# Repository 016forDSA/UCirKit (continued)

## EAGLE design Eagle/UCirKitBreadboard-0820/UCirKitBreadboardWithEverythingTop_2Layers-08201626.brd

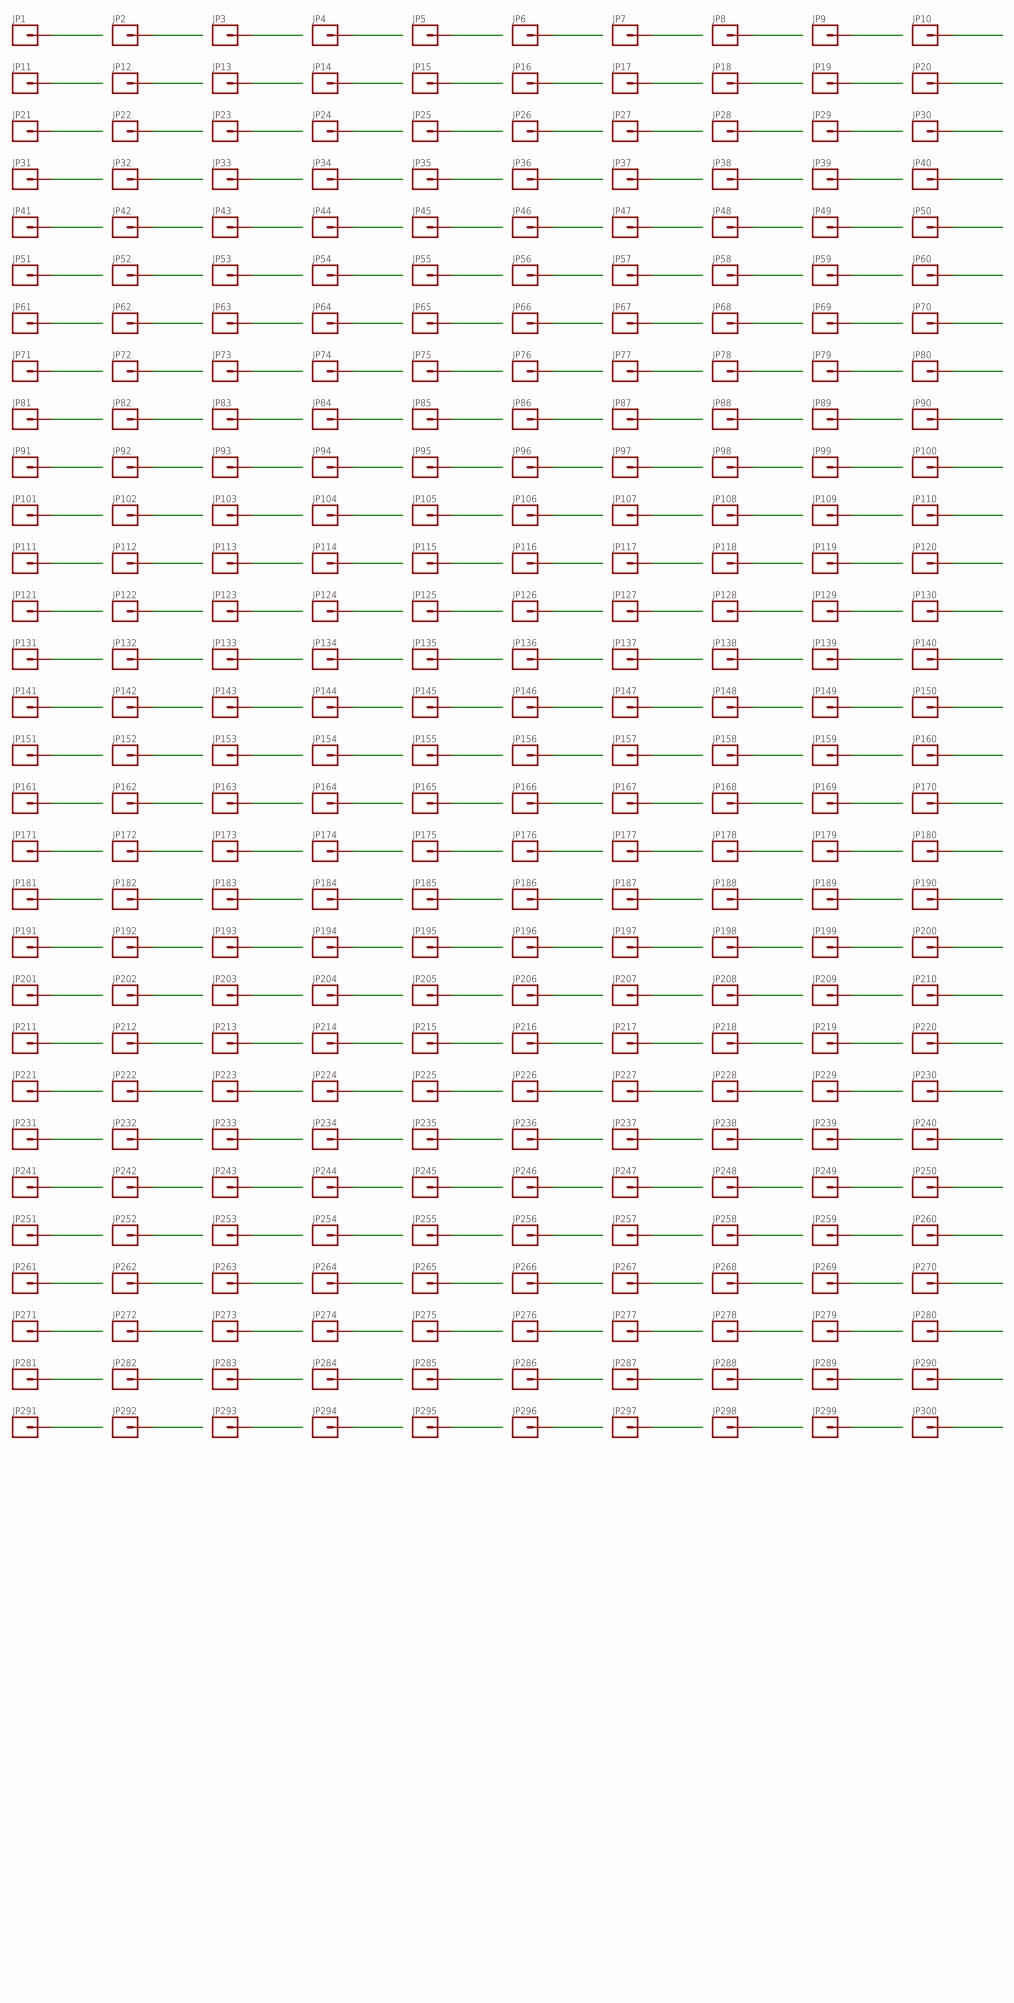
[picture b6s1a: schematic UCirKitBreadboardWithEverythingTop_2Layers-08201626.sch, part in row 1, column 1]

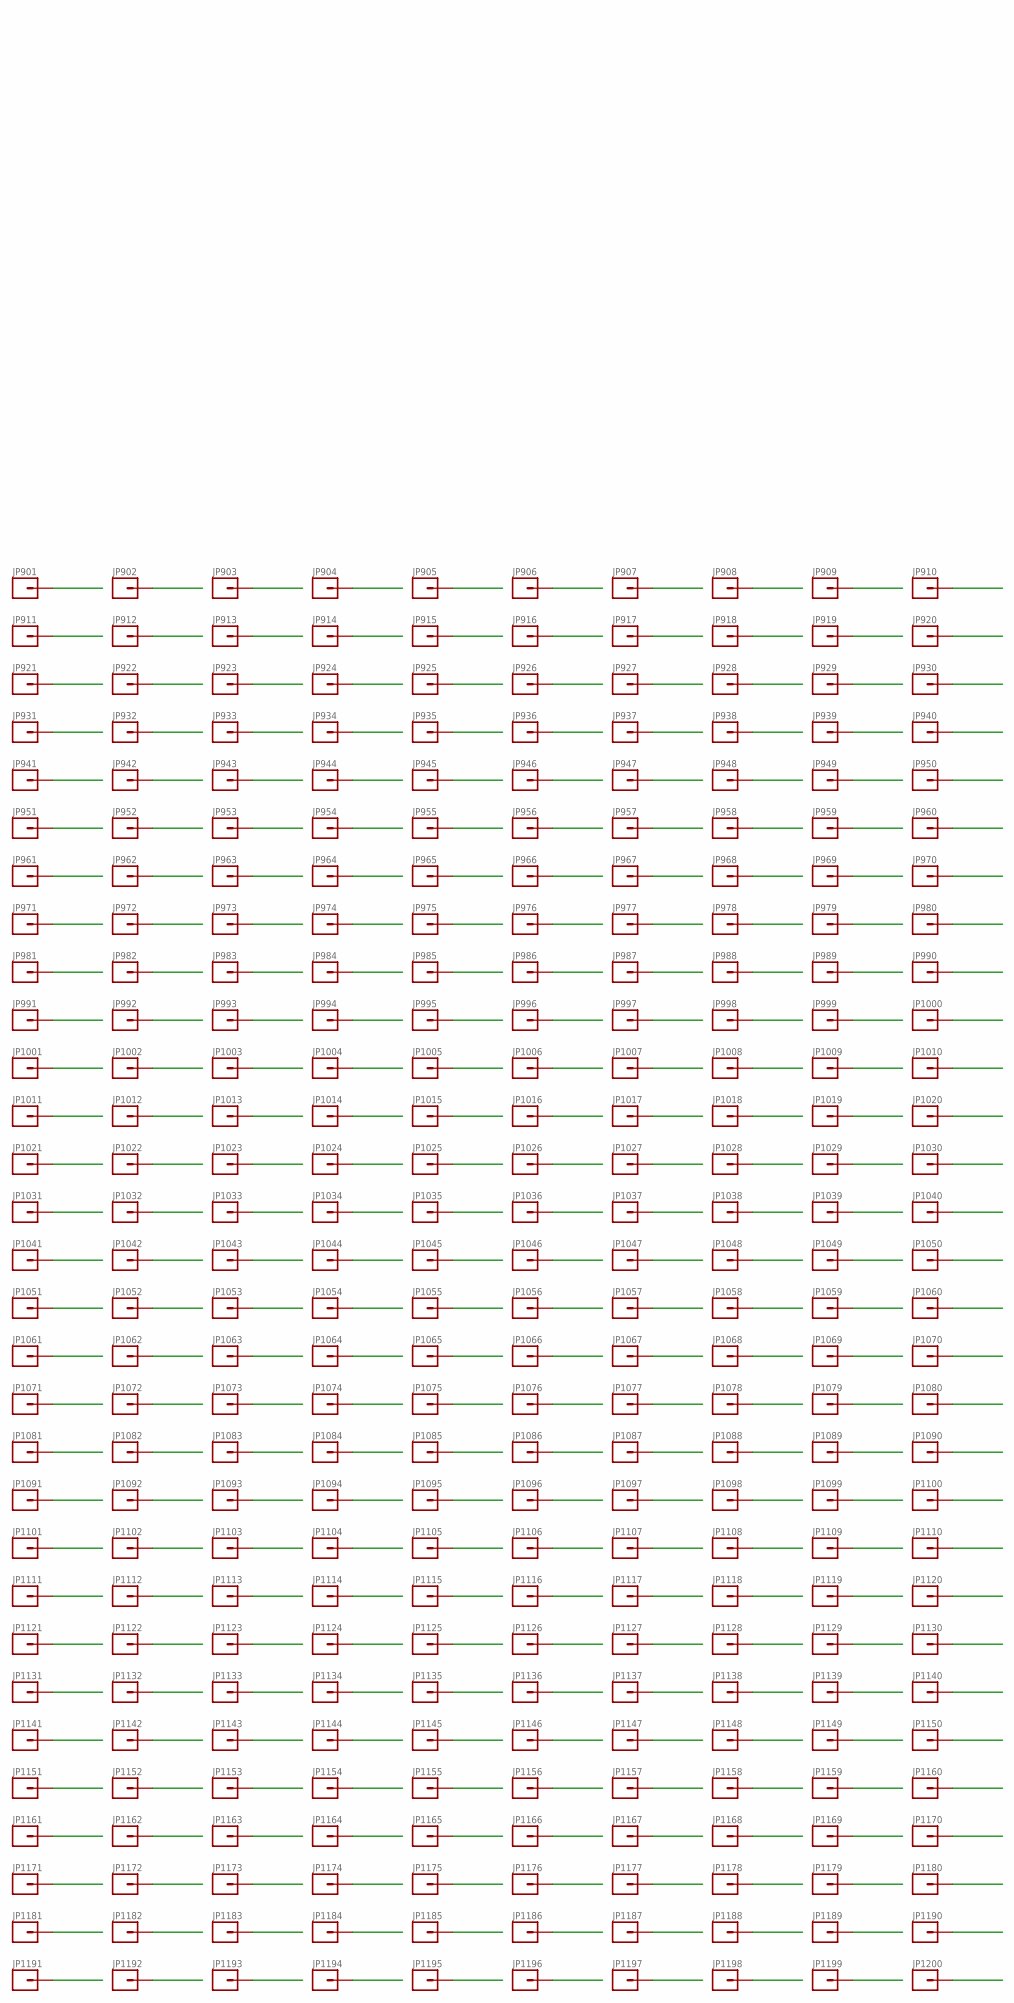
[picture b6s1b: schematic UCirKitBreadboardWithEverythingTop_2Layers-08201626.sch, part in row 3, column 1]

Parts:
JP1, JP2, JP3, JP4, JP5, JP6, JP7, JP8, JP9, JP10, JP11, JP12, JP13, JP14, JP15, JP16, JP17, JP18, JP19, JP20, JP21, JP22, JP23, JP24, JP25, JP26, JP27, JP28, JP29, JP30, JP31, JP32, JP33, JP34, JP35, JP36, JP37, JP38, JP39, JP40, JP41, JP42, JP43, JP44, JP45, JP46, JP47, JP48, JP49, JP50, JP51, JP52, JP53, JP54, JP55, JP56, JP57, JP58, JP59, JP60, JP61, JP62, JP63, JP64, JP65, JP66, JP67, JP68, JP69, JP70, JP71, JP72, JP73, JP74, JP75, JP76, JP77, JP78, JP79, JP80, JP81, JP82, JP83, JP84, JP85, JP86, JP87, JP88, JP89, JP90, JP91, JP92, JP93, JP94, JP95, JP96, JP97, JP98, JP99, JP100, JP101, JP102, JP103, JP104, JP105, JP106, JP107, JP108, JP109, JP110, JP111, JP112, JP113, JP114, JP115, JP116, JP117, JP118, JP119, JP120, JP121, JP122, JP123, JP124, JP125, JP126, JP127, JP128, JP129, JP130, JP131, JP132, JP133, JP134, JP135, JP136, JP137, JP138, JP139, JP140, JP141, JP142, JP143, JP144, JP145, JP146, JP147, JP148, JP149, JP150, JP151, JP152, JP153, JP154, JP155, JP156, JP157, JP158, JP159, JP160, JP161, JP162, JP163, JP164, JP165, JP166, JP167, JP168, JP169, JP170, JP171, JP172, JP173, JP174, JP175, JP176, JP177, JP178, JP179, JP180, JP181, JP182, JP183, JP184, JP185, JP186, JP187, JP188, JP189, JP190, JP191, JP192, JP193, JP194, JP195, JP196, JP197, JP198, JP199, JP200, JP201, JP202, JP203, JP204, JP205, JP206, JP207, JP208, JP209, JP210, JP211, JP212, JP213, JP214, JP215, JP216, JP217, JP218, JP219, JP220, JP221, JP222, JP223, JP224, JP225, JP226, JP227, JP228, JP229, JP230, JP231, JP232, JP233, JP234, JP235, JP236, JP237, JP238, JP239, JP240, JP241, JP242, JP243, JP244, JP245, JP246, JP247, JP248, JP249, JP250, JP251, JP252, JP253, JP254, JP255, JP256, JP257, JP258, JP259, JP260, JP261, JP262, JP263, JP264, JP265, JP266, JP267, JP268, JP269, JP270, JP271, JP272, JP273, JP274, JP275, JP276, JP277, JP278, JP279, JP280, JP281, JP282, JP283, JP284, JP285, JP286, JP287, JP288, JP289, JP290, JP291, JP292, JP293, JP294, JP295, JP296, JP297, JP298, JP299, JP300: M01PTH_WITHOUT_TEXT; 1X01_WITHOUT_TEXT
JP901, JP902, JP903, JP904, JP905, JP906, JP907, JP908, JP909, JP910, JP911, JP912, JP913, JP914, JP915, JP916, JP917, JP918, JP919, JP920, JP921, JP922, JP923, JP924, JP925, JP926, JP927, JP928, JP929, JP930, JP931, JP932, JP933, JP934, JP935, JP936, JP937, JP938, JP939, JP940, JP941, JP942, JP943, JP944, JP945, JP946, JP947, JP948, JP949, JP950, JP951, JP952, JP953, JP954, JP955, JP956, JP957, JP958, JP959, JP960, JP961, JP962, JP963, JP964, JP965, JP966, JP967, JP968, JP969, JP970, JP971, JP972, JP973, JP974, JP975, JP976, JP977, JP978, JP979, JP980, JP981, JP982, JP983, JP984, JP985, JP986, JP987, JP988, JP989, JP990, JP991, JP992, JP993, JP994, JP995, JP996, JP997, JP998, JP999, JP1000, JP1001, JP1002, JP1003, JP1004, JP1005, JP1006, JP1007, JP1008, JP1009, JP1010, JP1011, JP1012, JP1013, JP1014, JP1015, JP1016, JP1017, JP1018, JP1019, JP1020, JP1021, JP1022, JP1023, JP1024, JP1025, JP1026, JP1027, JP1028, JP1029, JP1030, JP1031, JP1032, JP1033, JP1034, JP1035, JP1036, JP1037, JP1038, JP1039, JP1040, JP1041, JP1042, JP1043, JP1044, JP1045, JP1046, JP1047, JP1048, JP1049, JP1050, JP1051, JP1052, JP1053, JP1054, JP1055, JP1056, JP1057, JP1058, JP1059, JP1060, JP1061, JP1062, JP1063, JP1064, JP1065, JP1066, JP1067, JP1068, JP1069, JP1070, JP1071, JP1072, JP1073, JP1074, JP1075, JP1076, JP1077, JP1078, JP1079, JP1080, JP1081, JP1082, JP1083, JP1084, JP1085, JP1086, JP1087, JP1088, JP1089, JP1090, JP1091, JP1092, JP1093, JP1094, JP1095, JP1096, JP1097, JP1098, JP1099, JP1100, JP1101, JP1102, JP1103, JP1104, JP1105, JP1106, JP1107, JP1108, JP1109, JP1110, JP1111, JP1112, JP1113, JP1114, JP1115, JP1116, JP1117, JP1118, JP1119, JP1120, JP1121, JP1122, JP1123, JP1124, JP1125, JP1126, JP1127, JP1128, JP1129, JP1130, JP1131, JP1132, JP1133, JP1134, JP1135, JP1136, JP1137, JP1138, JP1139, JP1140, JP1141, JP1142, JP1143, JP1144, JP1145, JP1146, JP1147, JP1148, JP1149, JP1150, JP1151, JP1152, JP1153, JP1154, JP1155, JP1156, JP1157, JP1158, JP1159, JP1160, JP1161, JP1162, JP1163, JP1164, JP1165, JP1166, JP1167, JP1168, JP1169, JP1170, JP1171, JP1172, JP1173, JP1174, JP1175, JP1176, JP1177, JP1178, JP1179, JP1180, JP1181, JP1182, JP1183, JP1184, JP1185, JP1186, JP1187, JP1188, JP1189, JP1190, JP1191, JP1192, JP1193, JP1194, JP1195, JP1196, JP1197, JP1198, JP1199, JP1200: M01PTH_SMD_3.25X0.85MM_NO_SILK; 1X01_SMD_3.25X0.85MM_NO_SILK

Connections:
0_1440127218: JP1.1, JP961.P$1
0_1440127248: JP10.1, JP1021.P$1
0_1440127317: JP5.1, JP1141.P$1
0_1440127347: JP15.1, JP1142.P$1
0_1440127366: JP25.1, JP1143.P$1
0_1440127382: JP35.1, JP1144.P$1
0_1440127392: JP45.1, JP1145.P$1
0_1440127421: JP55.1, JP1146.P$1
0_1440127430: JP65.1, JP1147.P$1
0_1440127608: JP75.1, JP1148.P$1
0_1440127617: JP85.1, JP1149.P$1
0_1440127627: JP95.1, JP1150.P$1
0_1440127700: JP105.1, JP1151.P$1
0_1440127712: JP115.1, JP1152.P$1
0_1440127720: JP125.1, JP1153.P$1
0_1440127729: JP135.1, JP1154.P$1
0_1440127744: JP145.1, JP1155.P$1
0_1440127816: JP155.1, JP1156.P$1
0_1440127828: JP165.1, JP1157.P$1
0_1440127838: JP175.1, JP1158.P$1
0_1440127850: JP185.1, JP1159.P$1
0_1440127870: JP195.1, JP1160.P$1
0_1440127904: JP295.1, JP1181.P$1
0_1440127914: JP285.1, JP1182.P$1
0_1440127944: JP275.1, JP1183.P$1
0_1440127955: JP265.1, JP1184.P$1
0_1440128006: JP255.1, JP1185.P$1
0_1440128015: JP245.1, JP1186.P$1
0_1440128025: JP235.1, JP1187.P$1
0_1440128039: JP225.1, JP1188.P$1
0_1440128052: JP215.1, JP1189.P$1
0_1440128062: JP205.1, JP1190.P$1
0_1440128088: JP6.1, JP1170.P$1
0_1440128098: JP16.1, JP1169.P$1
0_1440128106: JP26.1, JP1168.P$1
0_1440128116: JP36.1, JP1167.P$1
0_1440128126: JP46.1, JP1166.P$1
0_1440128135: JP56.1, JP1165.P$1
0_1440128149: JP66.1, JP1164.P$1
0_1440128159: JP76.1, JP1163.P$1
0_1440128167: JP86.1, JP1162.P$1
0_1440128175: JP96.1, JP1161.P$1
0_1440128223: JP106.1, JP1180.P$1
0_1440128233: JP116.1, JP1179.P$1
0_1440128243: JP126.1, JP1178.P$1
0_1440128252: JP136.1, JP1177.P$1
0_1440128264: JP146.1, JP1176.P$1
0_1440128275: JP156.1, JP1175.P$1
0_1440128290: JP166.1, JP1174.P$1
0_1440128302: JP176.1, JP1173.P$1
0_1440128314: JP186.1, JP1172.P$1
0_1440128326: JP196.1, JP1171.P$1
0_1440128344: JP296.1, JP1200.P$1
0_1440128353: JP286.1, JP1199.P$1
0_1440128363: JP276.1, JP1198.P$1
0_1440128375: JP266.1, JP1197.P$1
0_1440128386: JP256.1, JP1196.P$1
0_1440128396: JP246.1, JP1195.P$1
0_1440128405: JP236.1, JP1194.P$1
0_1440128414: JP226.1, JP1193.P$1
0_1440128424: JP216.1, JP1192.P$1
0_1440128432: JP206.1, JP1191.P$1
1_1440127218: JP11.1, JP963.P$1
1_1440127248: JP20.1, JP1023.P$1
2_1440127218: JP21.1, JP965.P$1
2_1440127248: JP30.1, JP1025.P$1
3_1440127218: JP31.1, JP967.P$1
3_1440127248: JP40.1, JP1027.P$1
4_1440127218: JP41.1, JP969.P$1
4_1440127248: JP50.1, JP1029.P$1
5_1440127218: JP51.1, JP971.P$1
5_1440127248: JP60.1, JP1031.P$1
6_1440127218: JP61.1, JP973.P$1
6_1440127248: JP70.1, JP1033.P$1
7_1440127218: JP71.1, JP975.P$1
7_1440127248: JP80.1, JP1035.P$1
8_1440127218: JP81.1, JP977.P$1
8_1440127248: JP90.1, JP1037.P$1
9_1440127218: JP91.1, JP979.P$1
9_1440127248: JP100.1, JP1039.P$1
10_1440127218: JP101.1, JP981.P$1
10_1440127248: JP110.1, JP1041.P$1
11_1440127218: JP111.1, JP983.P$1
11_1440127248: JP120.1, JP1043.P$1
12_1440127218: JP121.1, JP985.P$1
12_1440127248: JP130.1, JP1045.P$1
13_1440127218: JP131.1, JP987.P$1
13_1440127248: JP140.1, JP1047.P$1
14_1440127218: JP141.1, JP989.P$1
14_1440127248: JP150.1, JP1049.P$1
15_1440127218: JP151.1, JP991.P$1
15_1440127248: JP160.1, JP1051.P$1
16_1440127218: JP161.1, JP993.P$1
16_1440127248: JP170.1, JP1053.P$1
17_1440127218: JP171.1, JP995.P$1
17_1440127248: JP180.1, JP1055.P$1
18_1440127218: JP181.1, JP997.P$1
18_1440127248: JP190.1, JP1057.P$1
19_1440127218: JP191.1, JP999.P$1
19_1440127248: JP200.1, JP1059.P$1
20_1440127218: JP201.1, JP1001.P$1
20_1440127248: JP210.1, JP1061.P$1
21_1440127218: JP211.1, JP1003.P$1
21_1440127248: JP220.1, JP1063.P$1
22_1440127218: JP221.1, JP1005.P$1
22_1440127248: JP230.1, JP1065.P$1
23_1440127218: JP231.1, JP1007.P$1
23_1440127248: JP240.1, JP1067.P$1
24_1440127218: JP241.1, JP1009.P$1
24_1440127248: JP250.1, JP1069.P$1
25_1440127218: JP251.1, JP1011.P$1
25_1440127248: JP260.1, JP1071.P$1
26_1440127218: JP261.1, JP1013.P$1
26_1440127248: JP270.1, JP1073.P$1
27_1440127218: JP271.1, JP1015.P$1
27_1440127248: JP280.1, JP1075.P$1
28_1440127218: JP281.1, JP1017.P$1
28_1440127248: JP290.1, JP1077.P$1
29_1440127218: JP291.1, JP1019.P$1
29_1440127248: JP300.1, JP1079.P$1
30_1440127218: JP292.1, JP1020.P$1
30_1440127248: JP299.1, JP1080.P$1
31_1440127218: JP2.1, JP962.P$1
31_1440127248: JP9.1, JP1022.P$1
32_1440127218: JP12.1, JP964.P$1
32_1440127248: JP19.1, JP1024.P$1
33_1440127218: JP22.1, JP966.P$1
33_1440127248: JP29.1, JP1026.P$1
34_1440127218: JP32.1, JP968.P$1
34_1440127248: JP39.1, JP1028.P$1
35_1440127218: JP42.1, JP970.P$1
35_1440127248: JP49.1, JP1030.P$1
36_1440127218: JP52.1, JP972.P$1
36_1440127248: JP59.1, JP1032.P$1
37_1440127218: JP62.1, JP974.P$1
37_1440127248: JP69.1, JP1034.P$1
38_1440127218: JP72.1, JP976.P$1
38_1440127248: JP79.1, JP1036.P$1
39_1440127218: JP82.1, JP978.P$1
39_1440127248: JP89.1, JP1038.P$1
40_1440127218: JP92.1, JP980.P$1
40_1440127248: JP99.1, JP1040.P$1
41_1440127218: JP102.1, JP982.P$1
41_1440127248: JP109.1, JP1042.P$1
42_1440127218: JP112.1, JP984.P$1
42_1440127248: JP119.1, JP1044.P$1
43_1440127218: JP122.1, JP986.P$1
43_1440127248: JP129.1, JP1046.P$1
44_1440127218: JP132.1, JP988.P$1
44_1440127248: JP139.1, JP1048.P$1
45_1440127218: JP142.1, JP990.P$1
45_1440127248: JP149.1, JP1050.P$1
46_1440127218: JP152.1, JP992.P$1
46_1440127248: JP159.1, JP1052.P$1
47_1440127218: JP162.1, JP994.P$1
47_1440127248: JP169.1, JP1054.P$1
48_1440127218: JP172.1, JP996.P$1
48_1440127248: JP179.1, JP1056.P$1
49_1440127218: JP182.1, JP998.P$1
49_1440127248: JP189.1, JP1058.P$1
50_1440127218: JP192.1, JP1000.P$1
50_1440127248: JP199.1, JP1060.P$1
51_1440127218: JP202.1, JP1002.P$1
51_1440127248: JP209.1, JP1062.P$1
52_1440127218: JP212.1, JP1004.P$1
52_1440127248: JP219.1, JP1064.P$1
53_1440127218: JP222.1, JP1006.P$1
53_1440127248: JP229.1, JP1066.P$1
54_1440127218: JP232.1, JP1008.P$1
54_1440127248: JP239.1, JP1068.P$1
55_1440127218: JP242.1, JP1010.P$1
55_1440127248: JP249.1, JP1070.P$1
56_1440127218: JP252.1, JP1012.P$1
56_1440127248: JP259.1, JP1072.P$1
57_1440127218: JP262.1, JP1014.P$1
57_1440127248: JP269.1, JP1074.P$1
58_1440127218: JP272.1, JP1016.P$1
58_1440127248: JP279.1, JP1076.P$1
59_1440127218: JP282.1, JP1018.P$1
59_1440127248: JP289.1, JP1078.P$1
60_1440127218: JP3.1, JP901.P$1
60_1440127248: JP8.1, JP1081.P$1
61_1440127218: JP13.1, JP903.P$1
61_1440127248: JP18.1, JP1083.P$1
62_1440127218: JP23.1, JP905.P$1
62_1440127248: JP28.1, JP1085.P$1
63_1440127218: JP33.1, JP907.P$1
63_1440127248: JP38.1, JP1087.P$1
64_1440127218: JP43.1, JP909.P$1
64_1440127248: JP48.1, JP1089.P$1
65_1440127218: JP53.1, JP911.P$1
65_1440127248: JP58.1, JP1091.P$1
66_1440127218: JP63.1, JP913.P$1
66_1440127248: JP68.1, JP1093.P$1
67_1440127218: JP73.1, JP915.P$1
67_1440127248: JP78.1, JP1095.P$1
68_1440127218: JP83.1, JP917.P$1
68_1440127248: JP88.1, JP1097.P$1
69_1440127218: JP93.1, JP919.P$1
69_1440127248: JP98.1, JP1099.P$1
70_1440127218: JP103.1, JP921.P$1
70_1440127248: JP108.1, JP1101.P$1
71_1440127218: JP113.1, JP923.P$1
71_1440127248: JP118.1, JP1103.P$1
72_1440127218: JP123.1, JP925.P$1
72_1440127248: JP128.1, JP1105.P$1
73_1440127218: JP133.1, JP927.P$1
73_1440127248: JP138.1, JP1107.P$1
74_1440127218: JP143.1, JP929.P$1
74_1440127248: JP148.1, JP1109.P$1
75_1440127218: JP153.1, JP931.P$1
75_1440127248: JP158.1, JP1111.P$1
76_1440127218: JP163.1, JP933.P$1
76_1440127248: JP168.1, JP1113.P$1
77_1440127218: JP173.1, JP935.P$1
77_1440127248: JP178.1, JP1115.P$1
78_1440127218: JP183.1, JP937.P$1
78_1440127248: JP188.1, JP1117.P$1
79_1440127218: JP193.1, JP939.P$1
79_1440127248: JP198.1, JP1119.P$1
80_1440127218: JP203.1, JP941.P$1
80_1440127248: JP208.1, JP1121.P$1
81_1440127218: JP213.1, JP943.P$1
81_1440127248: JP218.1, JP1123.P$1
82_1440127218: JP223.1, JP945.P$1
82_1440127248: JP228.1, JP1125.P$1
83_1440127218: JP233.1, JP947.P$1
83_1440127248: JP238.1, JP1127.P$1
84_1440127218: JP243.1, JP949.P$1
84_1440127248: JP248.1, JP1129.P$1
85_1440127218: JP253.1, JP951.P$1
85_1440127248: JP258.1, JP1131.P$1
86_1440127218: JP263.1, JP953.P$1
86_1440127248: JP268.1, JP1133.P$1
87_1440127218: JP273.1, JP955.P$1
87_1440127248: JP278.1, JP1135.P$1
88_1440127218: JP283.1, JP957.P$1
88_1440127248: JP288.1, JP1137.P$1
89_1440127218: JP293.1, JP959.P$1
89_1440127248: JP298.1, JP1139.P$1
90_1440127218: JP294.1, JP960.P$1
90_1440127248: JP297.1, JP1140.P$1
91_1440127218: JP4.1, JP902.P$1
91_1440127248: JP7.1, JP1082.P$1
92_1440127218: JP14.1, JP904.P$1
92_1440127248: JP17.1, JP1084.P$1
93_1440127218: JP24.1, JP906.P$1
93_1440127248: JP27.1, JP1086.P$1
94_1440127218: JP34.1, JP908.P$1
94_1440127248: JP37.1, JP1088.P$1
95_1440127218: JP44.1, JP910.P$1
95_1440127248: JP47.1, JP1090.P$1
96_1440127218: JP54.1, JP912.P$1
96_1440127248: JP57.1, JP1092.P$1
97_1440127218: JP64.1, JP914.P$1
97_1440127248: JP67.1, JP1094.P$1
98_1440127218: JP74.1, JP916.P$1
98_1440127248: JP77.1, JP1096.P$1
99_1440127218: JP84.1, JP918.P$1
99_1440127248: JP87.1, JP1098.P$1
100_1440127218: JP94.1, JP920.P$1
100_1440127248: JP97.1, JP1100.P$1
101_1440127218: JP104.1, JP922.P$1
101_1440127248: JP107.1, JP1102.P$1
102_1440127218: JP114.1, JP924.P$1
102_1440127248: JP117.1, JP1104.P$1
103_1440127218: JP124.1, JP926.P$1
103_1440127248: JP127.1, JP1106.P$1
104_1440127218: JP134.1, JP928.P$1
104_1440127248: JP137.1, JP1108.P$1
105_1440127218: JP144.1, JP930.P$1
105_1440127248: JP147.1, JP1110.P$1
106_1440127218: JP154.1, JP932.P$1
106_1440127248: JP157.1, JP1112.P$1
107_1440127218: JP164.1, JP934.P$1
107_1440127248: JP167.1, JP1114.P$1
108_1440127218: JP174.1, JP936.P$1
108_1440127248: JP177.1, JP1116.P$1
109_1440127218: JP184.1, JP938.P$1
109_1440127248: JP187.1, JP1118.P$1
110_1440127218: JP194.1, JP940.P$1
110_1440127248: JP197.1, JP1120.P$1
111_1440127218: JP204.1, JP942.P$1
111_1440127248: JP207.1, JP1122.P$1
112_1440127218: JP214.1, JP944.P$1
112_1440127248: JP217.1, JP1124.P$1
113_1440127218: JP224.1, JP946.P$1
113_1440127248: JP227.1, JP1126.P$1
114_1440127218: JP234.1, JP948.P$1
114_1440127248: JP237.1, JP1128.P$1
115_1440127218: JP244.1, JP950.P$1
115_1440127248: JP247.1, JP1130.P$1
116_1440127218: JP254.1, JP952.P$1
116_1440127248: JP257.1, JP1132.P$1
117_1440127218: JP264.1, JP954.P$1
117_1440127248: JP267.1, JP1134.P$1
118_1440127218: JP274.1, JP956.P$1
118_1440127248: JP277.1, JP1136.P$1
119_1440127218: JP284.1, JP958.P$1
119_1440127248: JP287.1, JP1138.P$1

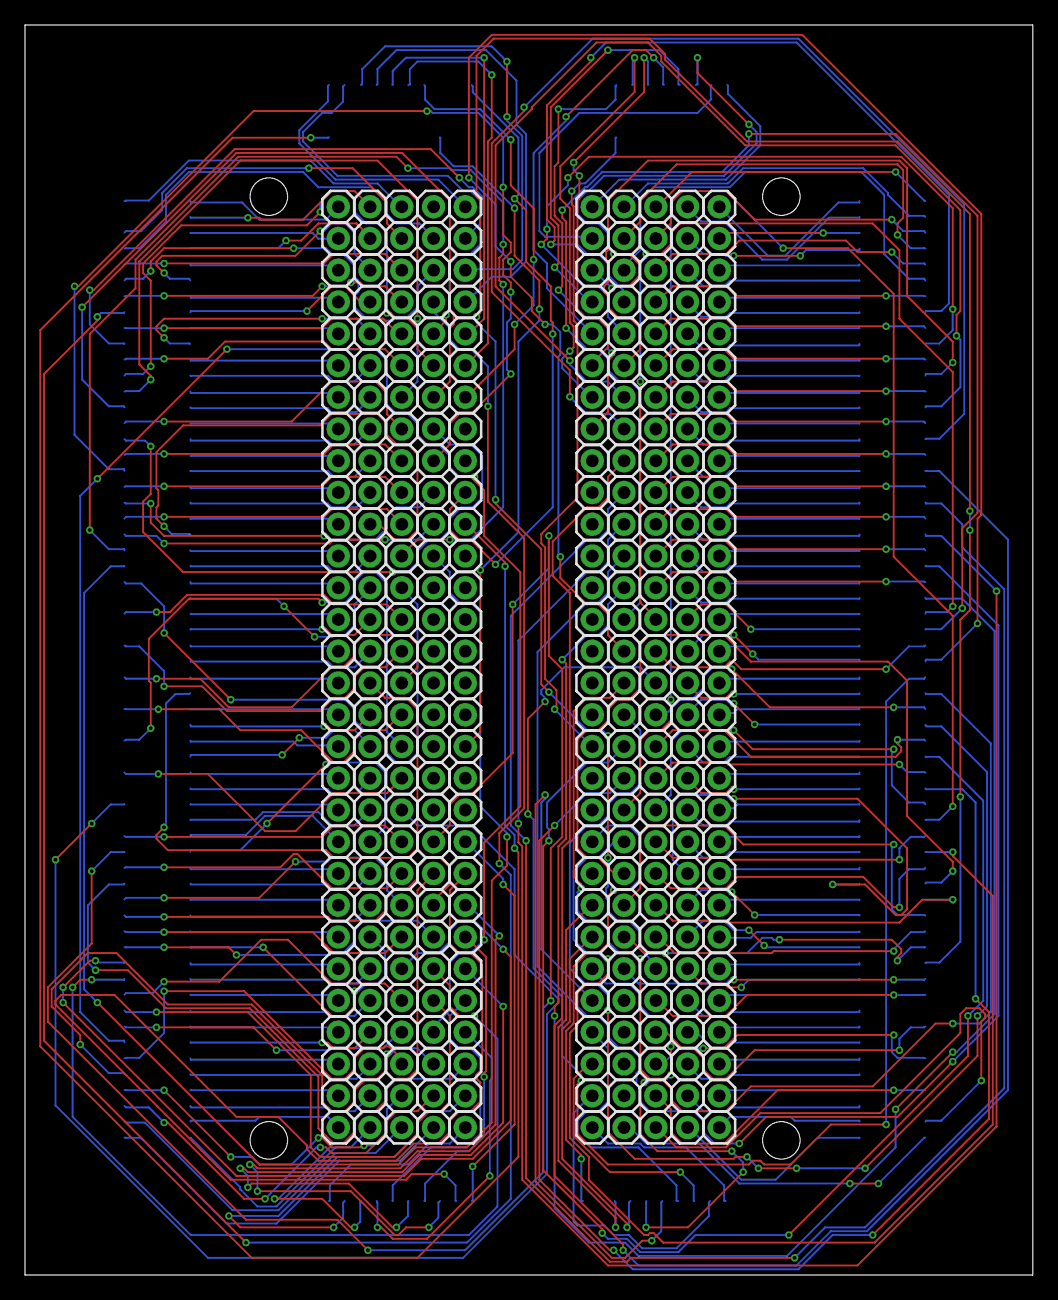
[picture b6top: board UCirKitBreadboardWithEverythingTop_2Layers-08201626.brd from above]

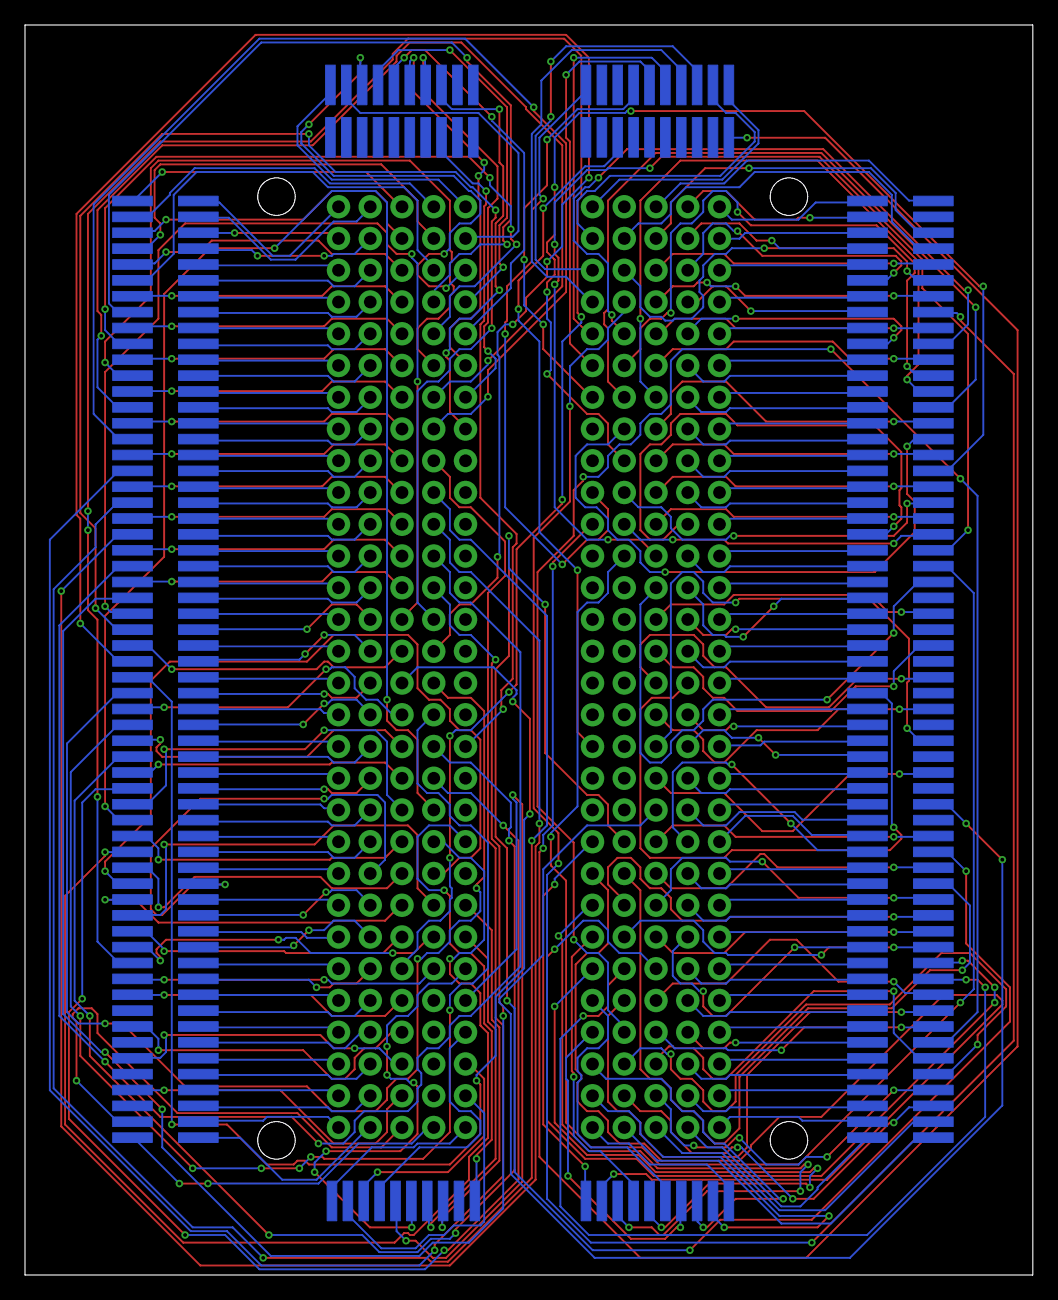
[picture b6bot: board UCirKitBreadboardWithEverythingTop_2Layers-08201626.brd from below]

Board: 2 copper layers, 80.6 x 100.0 mm, 600 parts (300 on the bottom side), 300 nets.
